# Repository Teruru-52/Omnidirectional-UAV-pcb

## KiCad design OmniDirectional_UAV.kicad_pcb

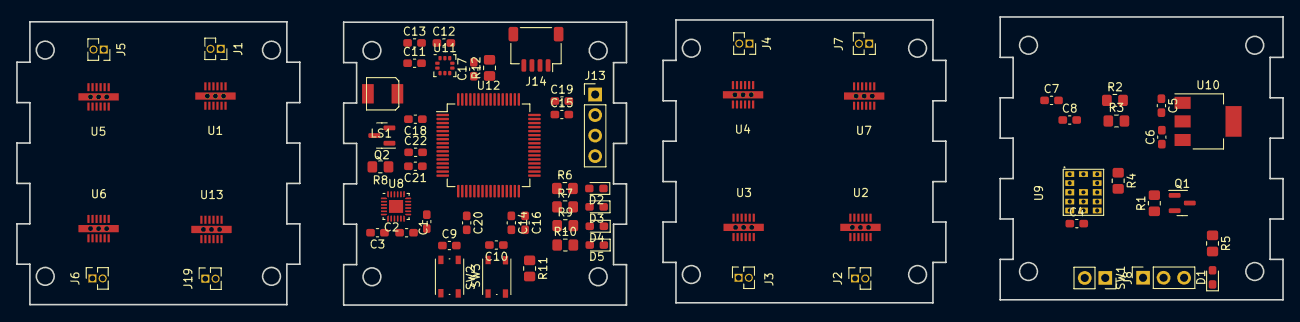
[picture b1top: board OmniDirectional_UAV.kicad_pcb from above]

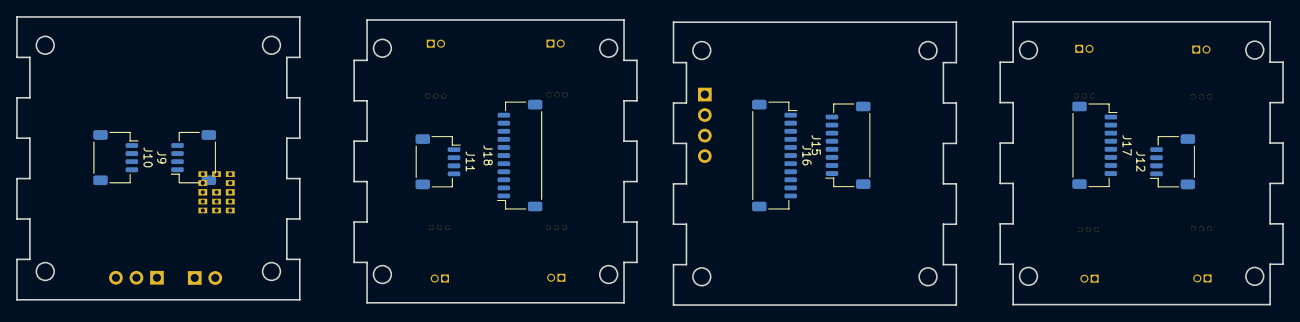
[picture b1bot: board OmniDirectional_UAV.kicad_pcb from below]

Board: 2 copper layers, 156.7 x 35.6 mm, 77 parts (8 on the bottom side), 95 nets, no tracks yet.

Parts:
C1, C21: 0.01u; C_0603_1608Metric_Pad1.08x0.95mm_HandSolder
C2, C3, C4, C7, C9, C10, C11, C13, C16, C17, C18, C19, C20: 0.1u; C_0603_1608Metric_Pad1.08x0.95mm_HandSolder
C5, C6, C12: 10u; C_0603_1608Metric_Pad1.08x0.95mm_HandSolder
C8: 20u; C_0603_1608Metric_Pad1.08x0.95mm_HandSolder
C14, C15: 2.2u; C_0603_1608Metric_Pad1.08x0.95mm_HandSolder
C22: 1u; C_0603_1608Metric_Pad1.08x0.95mm_HandSolder
D1, D2, D3, D4, D5: LED; LED_0603_1608Metric_Pad1.05x0.95mm_HandSolder
J1, J2, J3, J4, J5, J6, J7, J19: motor; PinSocket_1x02_P1.27mm_Vertical
J8: Conn_01x02; PinSocket_1x02_P2.54mm_Vertical
J9, J10, J11, J12: conn; JST_SH_SM04B-SRSS-TB_1x04-1MP_P1.00mm_Horizontal
J13: UART; PinHeader_1x04_P2.54mm_Vertical
J14: ST-Link; JST_SH_SM04B-SRSS-TB_1x04-1MP_P1.00mm_Horizontal
J15, J17: Conn_01x08_Female; JST_SH_SM08B-SRSS-TB_1x08-1MP_P1.00mm_Horizontal
J16, J18: Conn_01x11_Female; JST_SH_SM11B-SRSS-TB_1x11-1MP_P1.00mm_Horizontal
LS1: Speaker; STM0440-T-R
Q1: IRLML6402; SOT-23
Q2: BSS138; SOT-23
R1: 100k; R_0805_2012Metric_Pad1.20x1.40mm_HandSolder
R2: 20k; R_0805_2012Metric_Pad1.20x1.40mm_HandSolder
R3, R8, R11, R12: 10k; R_0805_2012Metric_Pad1.20x1.40mm_HandSolder
R4: 133; R_0805_2012Metric_Pad1.20x1.40mm_HandSolder
R5, R6, R7, R9, R10: 1k; R_0805_2012Metric_Pad1.20x1.40mm_HandSolder
SW1: SW_DPDT_x2; PinSocket_1x03_P2.54mm_Vertical
SW2, SW3: SKRPACE; SW_Push_1P1T_NO_Vertical_Wuerth_434133025816
U1, U2, U3, U4, U5, U6, U7, U13: DRV8835
U8: MPU9250; QFN-24-1EP_3x3mm_P0.4mm_EP1.75x1.6mm
U9: LXDC55FAAA-203; LXDC55FAA
U10: LT1963AES3-3.3; SOT-223
U11: LPS25HB; ST_HLGA-10_2.5x2.5mm_P0.6mm_LayoutBorder3x2y
U12: STM32F446RE; LQFP-64_10x10mm_P0.5mm

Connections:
+3.3V: C1.1, C3.1, C11.1, C12.1, C13.1, C16.1, C17.1, C18.1, C19.1, C20.1, C21.1, C22.1, J13.4, J16.10, LS1.1, R11.1, U8.1 (RESV), U8.8 (VDDIO), U8.13 (VDD), U11.1 (Vdd_IO), U11.10 (VDD), U12.1 (VBAT), U12.13 (VDDA), U12.19 (VDD), U12.32 (VDD), U12.48 (VDD), U12.64 (VDD)
+3.3V_: C6.1, J9.3, J10.3, R5.1, U10.3 (OUT)
+5V: C5.1, C7.1, C8.1, U9.7 (VOUT), U9.8 (VOUT), U9.9 (VOUT), U10.1 (IN)
+BATT: C4.1, J9.2, J10.2, Q1.3 (D), R2.1, U9.1 (EN), U9.3 (VIN), U9.4 (VIN), U9.5 (VIN)
/controller/+3.3V_: J11.2, J18.2, U2.12 (VCC), U3.12 (VCC), U4.12 (VCC), U7.12 (VCC)
/controller/ADC_BAT: J11.4, J18.4
/controller/BUTTON_OUTPUT: C10.1, R11.2, SW3.2 (D), U12.28 (PB2)
/controller/BUZZER_INPUT: Q2.1 (G), R8.1, U12.16 (PA2)
/controller/GND_: J11.1, J18.1, U2.6 (GND), U2.11 (MODE), U2.13 (GND_TP), U3.6 (GND), U3.11 (MODE), U3.13 (GND_TP), U4.6 (GND), U4.11 (MODE), U4.13 (GND_TP), U7.6 (GND), U7.11 (MODE), U7.13 (GND_TP)
/controller/LED1: R6.1, U12.36 (PB15)
/controller/LED2: R7.1, U12.35 (PB14)
/controller/LED3: R9.1, U12.34 (PB13)
/controller/LED4: R10.1, U12.33 (PB12)
/controller/MOTOR1_IN1: J18.8, U2.8 (BIN1), U2.10 (AIN1)
/controller/MOTOR1_IN2: J18.9, U2.7 (BIN2), U2.9 (AIN2)
/controller/MOTOR2_IN1: J17.8, U13.8 (BIN1), U13.10 (AIN1)
/controller/MOTOR2_IN2: J17.7, U13.7 (BIN2), U13.9 (AIN2)
/controller/MOTOR3_IN1: J18.10, U3.8 (BIN1), U3.10 (AIN1)
/controller/MOTOR3_IN2: J18.11, U3.7 (BIN2), U3.9 (AIN2)
/controller/MOTOR4_IN1: J18.3, U4.8 (BIN1), U4.10 (AIN1)
/controller/MOTOR4_IN2: J18.7, U4.7 (BIN2), U4.9 (AIN2)
/controller/MOTOR5_IN1: J17.1, U1.8 (BIN1), U1.10 (AIN1)
/controller/MOTOR5_IN2: J17.2, U1.7 (BIN2), U1.9 (AIN2)
/controller/MOTOR6_IN1: J17.3, U5.8 (BIN1), U5.10 (AIN1)
/controller/MOTOR6_IN2: J17.4, U5.7 (BIN2), U5.9 (AIN2)
/controller/MOTOR7_IN1: J17.5, U6.8 (BIN1), U6.10 (AIN1)
/controller/MOTOR7_IN2: J17.6, U6.7 (BIN2), U6.9 (AIN2)
/controller/MOTOR8_IN1: J18.5, U7.8 (BIN1), U7.10 (AIN1)
/controller/MOTOR8_IN2: J18.6, U7.7 (BIN2), U7.9 (AIN2)
/controller/NRST: C9.1, J14.4, SW2.2 (D), U12.7 (NRST)
/controller/SPI1_CS: U8.22 (nCS), U12.20 (PA4)
/controller/SPI1_MISO: U8.9 (ADO/SDO), U12.22 (PA6)
/controller/SPI1_MOSI: U8.24 (SDA/SDI), U12.23 (PA7)
/controller/SPI1_SCK: U8.23 (SCL/SCLK), U12.21 (PA5)
/controller/SPI3_CS: U11.6 (CS), U12.10 (PC2)
/controller/SPI3_MISO: U11.5 (SDO/SAO), U12.52 (PC11)
/controller/SPI3_MOSI: U11.4 (SDA/SDI/SDO), U12.9 (PC1)
/controller/SPI3_SCK: U11.2 (SLC/SPC), U12.51 (PC10)
/controller/SWCLK: J14.1, U12.49 (PA14)
/controller/SWDIO: J14.2, U12.46 (PA13)
/controller/USART1_RX: J13.1, U12.43 (PA10)
/controller/USART1_TX: J13.2, U12.42 (PA9)
/motor1/+BATT_1: J11.3, U2.1 (VM), U3.1 (VM), U4.1 (VM), U7.1 (VM)
/motor2/+3.3V_2: J12.3, U1.12 (VCC), U5.12 (VCC), U6.12 (VCC), U13.12 (VCC)
/motor2/+BATT_2: J12.4, U1.1 (VM), U5.1 (VM), U6.1 (VM), U13.1 (VM)
/motor2/GND_2: J12.2, U1.6 (GND), U1.11 (MODE), U1.13 (GND_TP), U5.6 (GND), U5.11 (MODE), U5.13 (GND_TP), U6.6 (GND), U6.11 (MODE), U6.13 (GND_TP), U13.6 (GND), U13.11 (MODE), U13.13 (GND_TP)
ADC_BAT_: J16.8, U12.27 (PB1)
BOOT0: R12.1, U12.60 (BOOT0)
GND: C1.2, C2.2, C3.2, C9.2, C10.2, C11.2, C12.2, C13.2, C14.2, C15.2, C16.2, C17.2, C18.2, C19.2, C20.2, C21.2, C22.2, D2.1 (K), D3.1 (K), D4.1 (K), D5.1 (K), J13.3, J14.3, J16.11, Q2.2 (S), R8.2, R12.2, SW2.1 (C), SW3.1 (C), U8.11 (FSYNC), U8.18 (GND), U8.20 (RESV), U11.3 (GND), U11.8 (GND), U11.9 (GND), U12.12 (VSSA), U12.18 (VSS), U12.31 (VSS), U12.63 (VSS)
GND_: C4.2, C5.2, C6.2, C7.2, C8.2, D1.1 (K), J8.2, J10.4, R3.2, R4.2, U9.6 (GND), U9.10 (PG), U9.12 (GND), U9.13 (GND), U9.14 (GND), U10.2 (GND), U10.4 (GND)
unnamed: C2.1, U8.10 (REGOUT)
unnamed: C14.1, U12.30 (VCAP)
unnamed: C15.1, U12.47 (VCAP_2)
unnamed: D1.2 (A), R5.2
unnamed: D2.2 (A), R6.2
unnamed: D3.2 (A), R7.2
unnamed: D4.2 (A), R9.2
unnamed: D5.2 (A), R10.2
unnamed: J1.1, U1.2 (AOUT1), U1.4 (BOUT1)
unnamed: J1.2, U1.3 (AOUT2), U1.5 (BOUT2)
unnamed: J2.1, U2.2 (AOUT1), U2.4 (BOUT1)
unnamed: J2.2, U2.3 (AOUT2), U2.5 (BOUT2)
unnamed: J3.1, U3.2 (AOUT1), U3.4 (BOUT1)
unnamed: J3.2, U3.3 (AOUT2), U3.5 (BOUT2)
unnamed: J4.1, U4.2 (AOUT1), U4.4 (BOUT1)
unnamed: J4.2, U4.3 (AOUT2), U4.5 (BOUT2)
unnamed: J5.1, U5.2 (AOUT1), U5.4 (BOUT1)
unnamed: J5.2, U5.3 (AOUT2), U5.5 (BOUT2)
unnamed: J6.1, U6.2 (AOUT1), U6.4 (BOUT1)
unnamed: J6.2, U6.3 (AOUT2), U6.5 (BOUT2)
unnamed: J7.1, U7.2 (AOUT1), U7.4 (BOUT1)
unnamed: J7.2, U7.3 (AOUT2), U7.5 (BOUT2)
unnamed: J8.1, Q1.2 (S), R1.1
unnamed: J19.1, U13.2 (AOUT1), U13.4 (BOUT1)
unnamed: J19.2, U13.3 (AOUT2), U13.5 (BOUT2)
unnamed: LS1.2, Q2.3 (D)
unnamed: Q1.1 (G), R1.2, SW1.2 (B)
unnamed: R4.1, U9.11 (FB)
_ADC_BAT: J9.1, R2.2, R3.1
_MOTOR1_IN1: J16.4, U12.50 (PA15)
_MOTOR1_IN2: J16.3, U12.55 (PB3)
_MOTOR2_IN1: J15.1, U12.29 (PB10)
_MOTOR2_IN2: J15.2, U12.17 (PA3)
_MOTOR3_IN1: J16.2, U12.56 (PB4)
_MOTOR3_IN2: J16.1, U12.57 (PB5)
_MOTOR4_IN1: J16.9, U12.26 (PB0)
_MOTOR4_IN2: J16.5, U12.40 (PC9)
_MOTOR5_IN1: J15.8, U12.58 (PB6)
_MOTOR5_IN2: J15.7, U12.59 (PB7)
_MOTOR6_IN1: J15.6, U12.61 (PB8)
_MOTOR6_IN2: J15.5, U12.62 (PB9)
_MOTOR7_IN1: J15.4, U12.14 (PA0_WKUP)
_MOTOR7_IN2: J15.3, U12.15 (PA1)
_MOTOR8_IN1: J16.7, U12.37 (PC6)
_MOTOR8_IN2: J16.6, U12.38 (PC7)

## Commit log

2022-11-01 add circuits
2022-12-06 add hierarchical sheets
2023-02-21 回路設計済
2023-02-21 update pcb
2023-02-21 部品配置完了
2023-02-21 pcb完成
